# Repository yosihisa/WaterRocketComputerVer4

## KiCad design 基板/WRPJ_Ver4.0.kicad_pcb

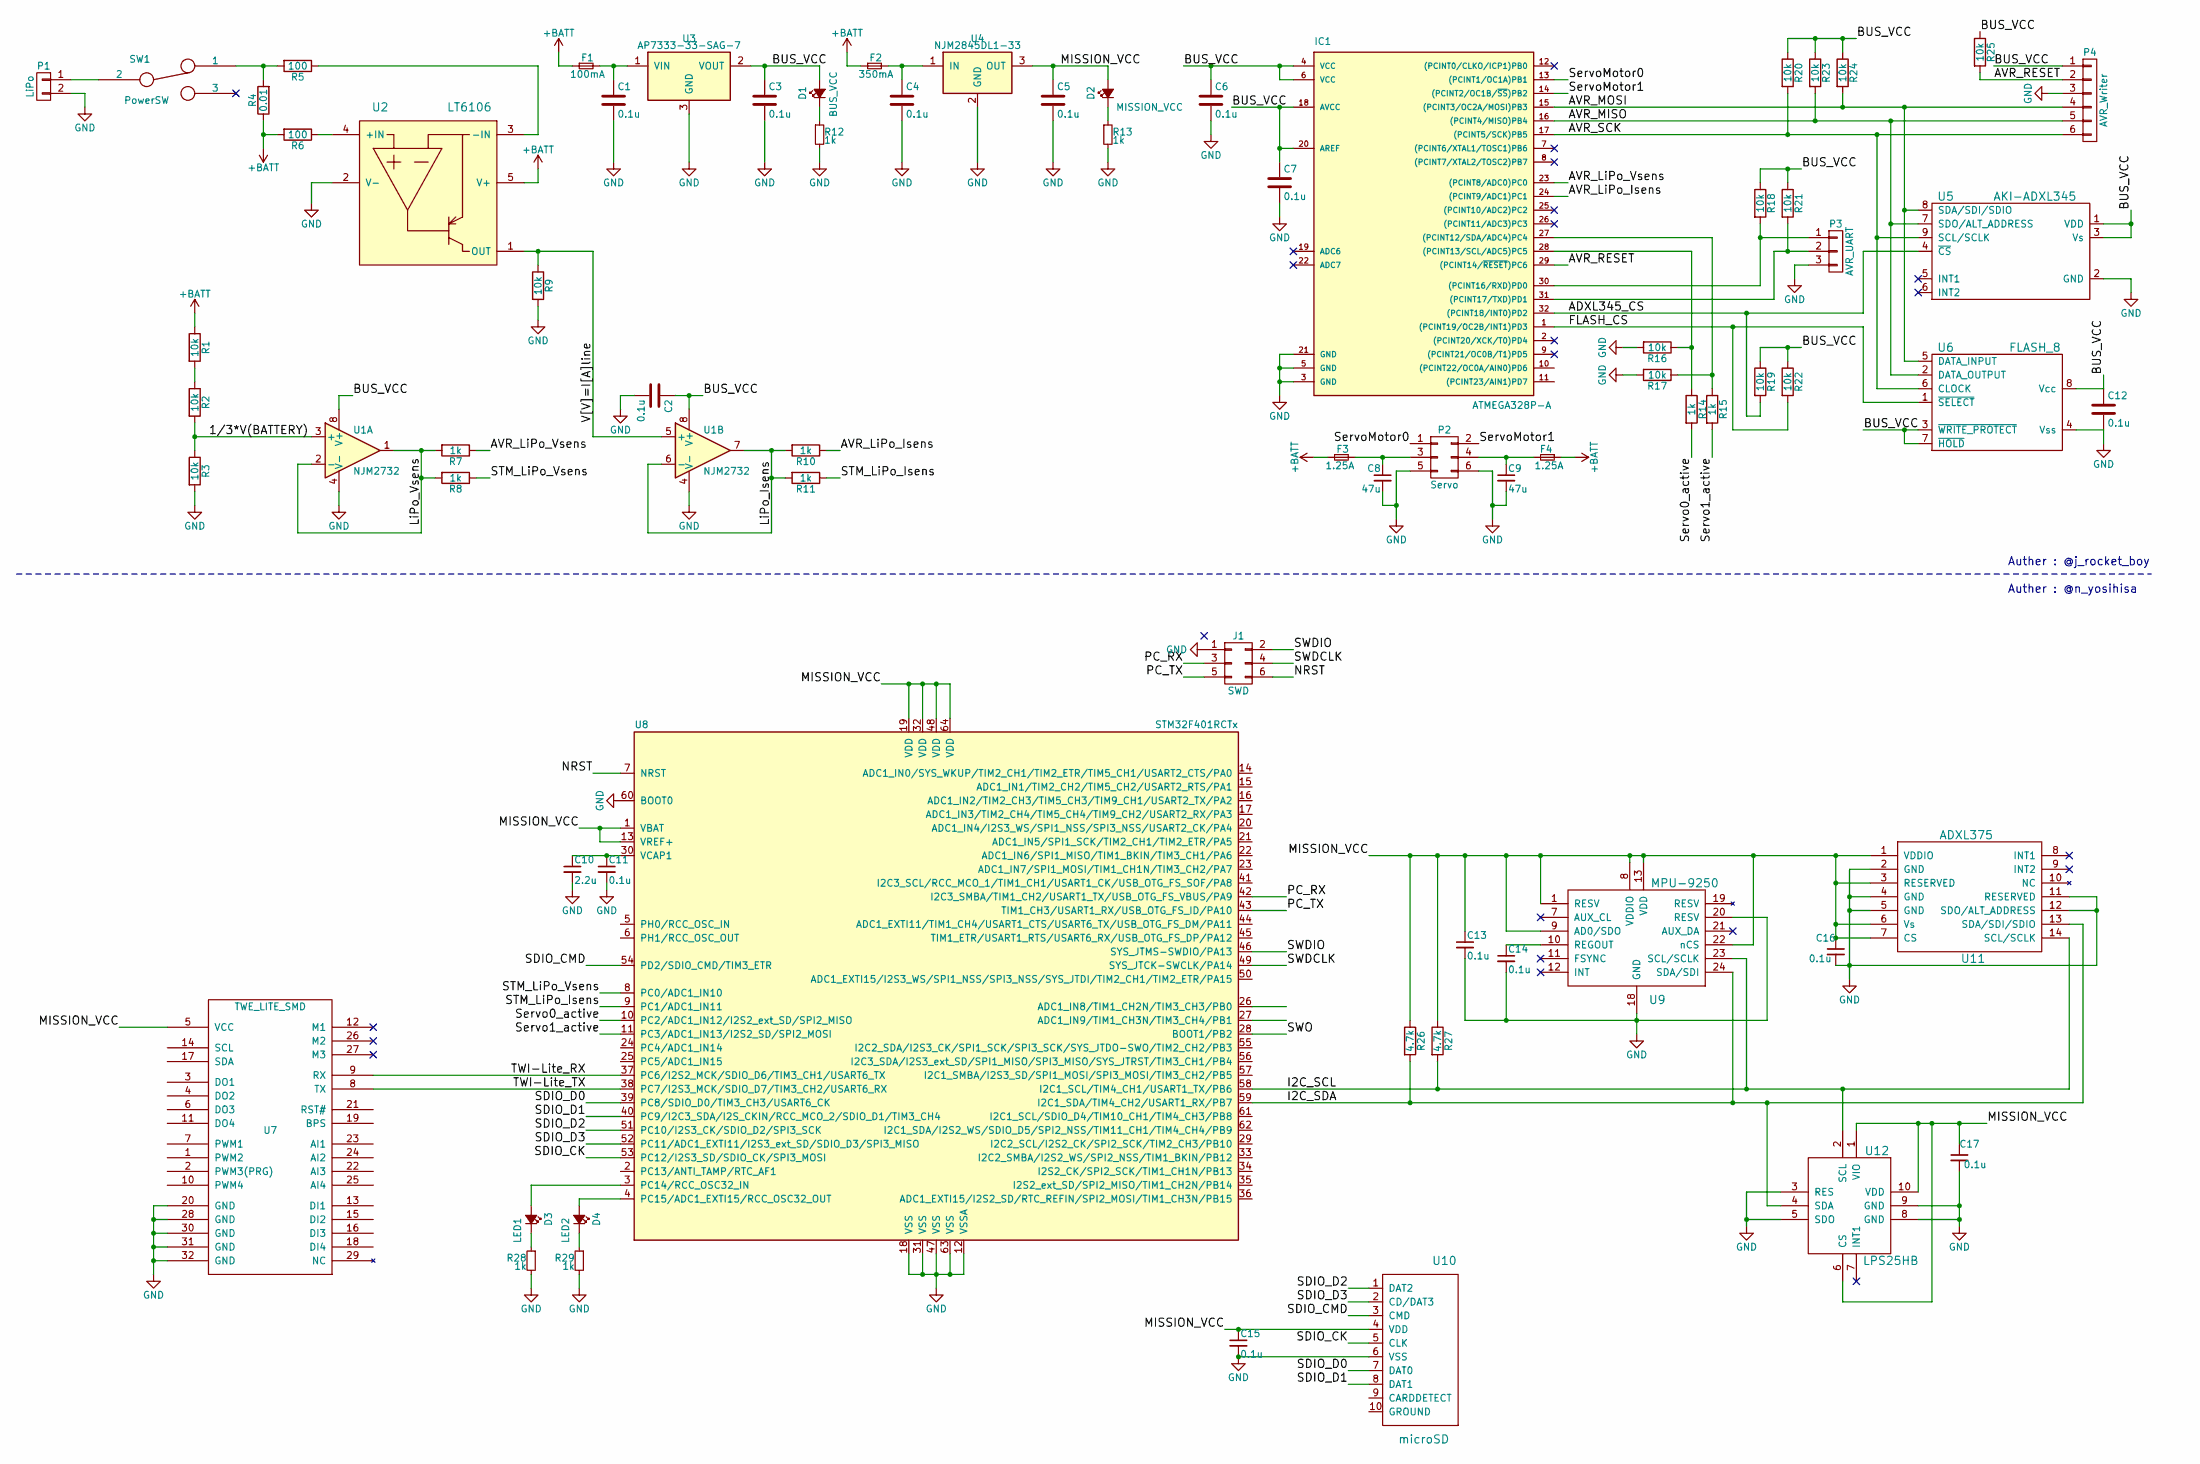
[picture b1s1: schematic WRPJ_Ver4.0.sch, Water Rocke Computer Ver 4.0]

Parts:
C1, C2, C3, C4, C5, C6, C7, C11, C12, C13, C14, C15, C16, C17: 0.1u; C_0603
C8, C9: 47u; C_1210
C10: 2.2u; C_0603
D1: BUS_VCC; LED_0603
D2: MISSION_VCC; LED_0603
D3: LED1; LED_0603
D4: LED2; LED_0603
F1: 100mA; R_1210
F2: 350mA; R_1210
F3, F4: 1.25A; R_1210
IC1: ATMEGA328P-A; LQFP-32_7x7mm_Pitch0.8mm
J1: SWD; Pin_Header_Straight_2x03_Pitch1.27mm
P1: LiPo; S2B-EH
P2: Servo; Pin_Header_Angled_2x03_Pitch2.54mm
P3: AVR_UART; Pin_Header_Straight_1x03_Pitch1.27mm
P4: AVR_Writer; Pin_Header_Straight_1x06_Pitch1.27mm
R1, R2, R3, R9, R16, R17, R18, R19, R20, R21, R22, R23, R24, R25: 10k; R_0603
R4: 0.01; R_2512
R5, R6: 100; R_0603
R7, R8, R10, R11, R12, R13, R14, R15, R28, R29: 1k; R_0603
R26, R27: 4.7k; R_0603
SW1: PowerSW; SS-12D01-VG4
U1: NJM2732; SSOP-8
U2: LT6106; SOT-23-5
U3: AP7333-33-SAG-7; SOT-23
U4: NJM2845DL1-33; TO-252-2
U5: AKI-ADXL345
U6: FLASH_8; SOIC-8-N
U7: TWE_LITE_SMD; TWE-001L-SMD
U8: STM32F401RCTx; LQFP-64_10x10mm_Pitch0.5mm
U9: MPU-9250; QFN-24_3x3mm_Pitch0.4mm
U10: microSD
U11: ADXL375; LGA_CC-14-1
U12: LPS25HB; HLGA-10L

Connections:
+BATT: F1.1, F2.1, F3.1, F4.1, R1.1, R4.1, R6.2, U2.5 (V+)
/1/3*V(BATTERY): R2.2, R3.1, U1.3 (+)
/ADXL345_CS: IC1.32 ((PCINT18/INT0)PD2), R19.2, U5.4 (~CS)
/AVR_LiPo_Isens: IC1.24 ((PCINT9/ADC1)PC1), R10.1
/AVR_LiPo_Vsens: IC1.23 ((PCINT8/ADC0)PC0), R7.1
/AVR_MISO: IC1.16 ((PCINT4/MISO)PB4), P4.5, R23.2, U5.7 (SDO/ALT_ADDRESS), U6.2 (DATA_OUTPUT)
/AVR_MOSI: IC1.15 ((PCINT3/OC2A/MOSI)PB3), P4.4, R24.2, U5.8 (SDA/SDI/SDIO), U6.5 (DATA_INPUT)
/AVR_RESET: IC1.29 ((PCINT14/~RESET~)PC6), P4.2, R25.2
/AVR_SCK: IC1.17 ((PCINT5/SCK)PB5), P4.6, R20.2, U5.9 (SCL/SCLK), U6.6 (CLOCK)
/BUS_VCC: C2.1, C3.1, C6.1, C7.1, C12.1, D1.2 (A), IC1.4 (VCC), IC1.6 (VCC), IC1.18 (AVCC), IC1.20 (AREF), P4.1, R18.1, R19.1, R20.1, R21.1, R22.1, R23.1, R24.1, R25.1, U1.8 (V+), U3.2 (VOUT), U5.1 (VDD), U5.3 (Vs), U6.3 (~WRITE_PROTECT), U6.7 (~HOLD), U6.8 (Vcc)
/FLASH_CS: IC1.1 ((PCINT19/OC2B/INT1)PD3), R22.2, U6.1 (~SELECT)
/I2C_SCL: R27.2, U8.58 (I2C1_SCL/TIM4_CH1/USART1_TX/PB6), U9.23 (SCL/SCLK), U11.14 (SCL/SCLK), U12.2 (SCL)
/I2C_SDA: R26.2, U8.59 (I2C1_SDA/TIM4_CH2/USART1_RX/PB7), U9.24 (SDA/SDI), U11.13 (SDA/SDI/SDIO), U12.4 (SDA)
/LiPo_Isens: R10.2, R11.2, U1.6 (-), U1.7
/LiPo_Vsens: R7.2, R8.2, U1.1, U1.2 (-)
/MISSION_VCC: C5.1, C13.1, C15.1, C16.1, C17.1, D2.2 (A), R26.1, R27.1, U4.3 (OUT), U7.5 (VCC), U8.1 (VBAT), U8.13 (VREF+), U8.19 (VDD), U8.32 (VDD), U8.48 (VDD), U8.64 (VDD), U9.1 (RESV), U9.8 (VDDIO), U9.9 (AD0/SDO), U9.13 (VDD), U9.22 (nCS), U10.4 (VDD), U11.1 (VDDIO), U11.3 (RESERVED), U11.6 (Vs), U11.7 (CS), U12.1 (VIO), U12.6 (CS), U12.10 (VDD)
/NRST: J1.6, U8.7 (NRST)
/PC_RX: J1.3, U8.42 (I2C3_SMBA/TIM1_CH2/USART1_TX/USB_OTG_FS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)
/PC_TX: J1.5, U8.43 (TIM1_CH3/USART1_RX/USB_OTG_FS_ID/PA10)
/SDIO_CK: U8.53 (PC12/I2S3_SD/SDIO_CK/SPI3_MOSI), U10.5 (CLK)
/SDIO_CMD: U8.54 (PD2/SDIO_CMD/TIM3_ETR), U10.3 (CMD)
/SDIO_D0: U8.39 (PC8/SDIO_D0/TIM3_CH3/USART6_CK), U10.7 (DAT0)
/SDIO_D1: U8.40 (PC9/I2C3_SDA/I2S_CKIN/RCC_MCO_2/SDIO_D1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), U10.8 (DAT1)
/SDIO_D2: U8.51 (PC10/I2S3_CK/SDIO_D2/SPI3_SCK), U10.1 (DAT2)
/SDIO_D3: U8.52 (PC11/ADC1_EXTI11/I2S3_ext_SD/SDIO_D3/SP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), U10.2 (CD/DAT3)
/STM_LiPo_Isens: R11.1, U8.9 (PC1/ADC1_IN11)
/STM_LiPo_Vsens: R8.1, U8.8 (PC0/ADC1_IN10)
/SWDCLK: J1.4, U8.49 (SYS_JTCK-SWCLK/PA14)
/SWDIO: J1.2, U8.46 (SYS_JTMS-SWDIO/PA13)
/SWO: U8.28 (BOOT1/PB2)
/Servo0_active: R14.2, U8.10 (PC2/ADC1_IN12/I2S2_ext_SD/SPI2_MISO)
/Servo1_active: R15.2, U8.11 (PC3/ADC1_IN13/I2S2_SD/SPI2_MOSI)
/ServoMotor0: IC1.13 ((PCINT1/OC1A)PB1), P2.1
/ServoMotor1: IC1.14 ((PCINT2/OC1B/~SS~)PB2), P2.2
/TWI-Lite_RX: U7.9 (RX), U8.37 (PC6/I2S2_MCK/SDIO_D6/TIM3_CH1/USART6_TX)
/TWI-Lite_TX: U7.8 (TX), U8.38 (PC7/I2S3_MCK/SDIO_D7/TIM3_CH2/USART6_RX)
/V[V]=I[A]line: R9.1, U1.5 (+), U2.1 (OUT)
GND: C1.2, C2.2, C3.2, C4.2, C5.2, C6.2, C7.2, C8.2, C9.2, C10.2, C11.2, C12.2, C13.2, C14.2, C15.2, C16.2, C17.2, IC1.3 (GND), IC1.5 (GND), IC1.21 (GND), J1.1, P1.2, P2.5, P2.6, P3.3, P4.3, R3.2, R9.2, R12.2, R13.2, R16.2, R17.2, R28.2, R29.2, U1.4 (V-), U2.2 (V-), U3.3 (GND), U4.2 (GND), U5.2 (GND), U6.4 (Vss), U7.20 (GND), U7.28 (GND), U7.30 (GND), U7.31 (GND), U7.32 (GND), U8.12 (VSSA), U8.18 (VSS), U8.31 (VSS), U8.47 (VSS), U8.60 (BOOT0), U8.63 (VSS), U9.18 (GND), U9.20 (RESV), U10.6 (VSS), U11.2 (GND), U11.4 (GND), U11.5 (GND), U11.11 (RESERVED), U11.12 (SDO/ALT_ADDRESS), U12.3 (RES), U12.5 (SDO), U12.8 (GND), U12.9 (GND)
unnamed: C1.1, F1.2, U3.1 (VIN)
unnamed: C4.1, F2.2, U4.1 (IN)
unnamed: C8.1, F3.2, P2.3
unnamed: C9.1, F4.2, P2.4
unnamed: C10.1, C11.1, U8.30 (VCAP1)
unnamed: C14.1, U9.10 (REGOUT)
unnamed: D1.1 (K), R12.1
unnamed: D2.1 (K), R13.1
unnamed: D3.1 (K), R28.1
unnamed: D3.2 (A), U8.3 (PC14/RCC_OSC32_IN)
unnamed: D4.1 (K), R29.1
unnamed: D4.2 (A), U8.4 (PC15/ADC1_EXTI15/RCC_OSC32_OUT)
unnamed: IC1.27 ((PCINT12/SDA/ADC4)PC4), R15.1, R17.1
unnamed: IC1.28 ((PCINT13/SCL/ADC5)PC5), R14.1, R16.1
unnamed: IC1.30 ((PCINT16/RXD)PD0), P3.1, R18.2
unnamed: IC1.31 ((PCINT17/TXD)PD1), P3.2, R21.2
unnamed: P1.1, SW1.2
unnamed: R1.2, R2.1
unnamed: R4.2, R5.2, SW1.1
unnamed: R5.1, U2.3 (-IN)
unnamed: R6.1, U2.4 (+IN)

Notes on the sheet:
Auther : @j_rocket_boy
Auther : @n_yosihisa

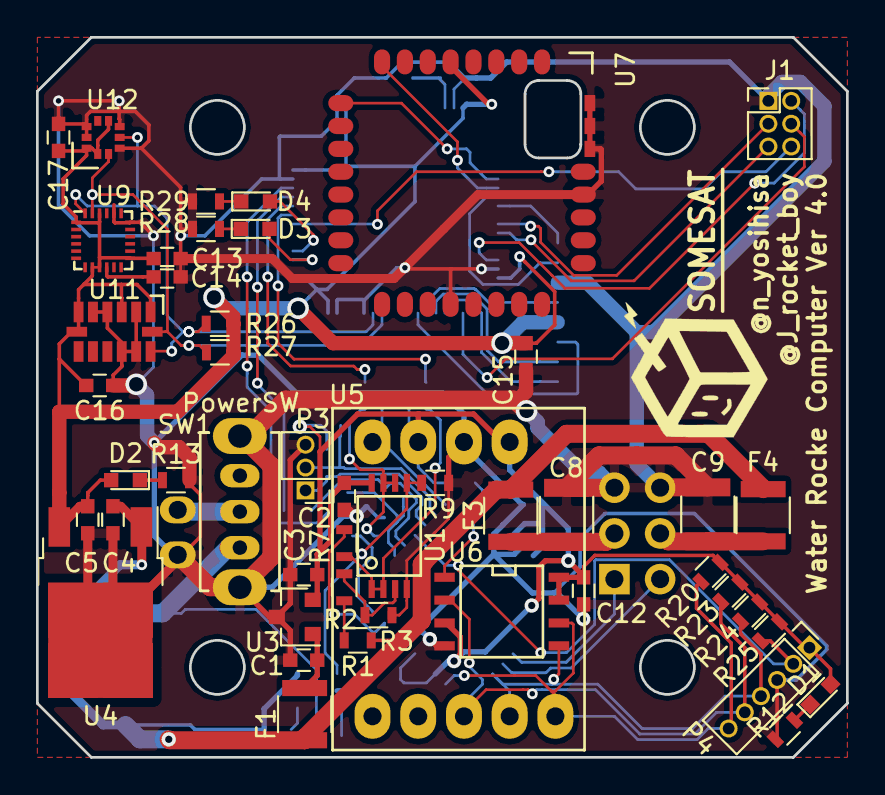
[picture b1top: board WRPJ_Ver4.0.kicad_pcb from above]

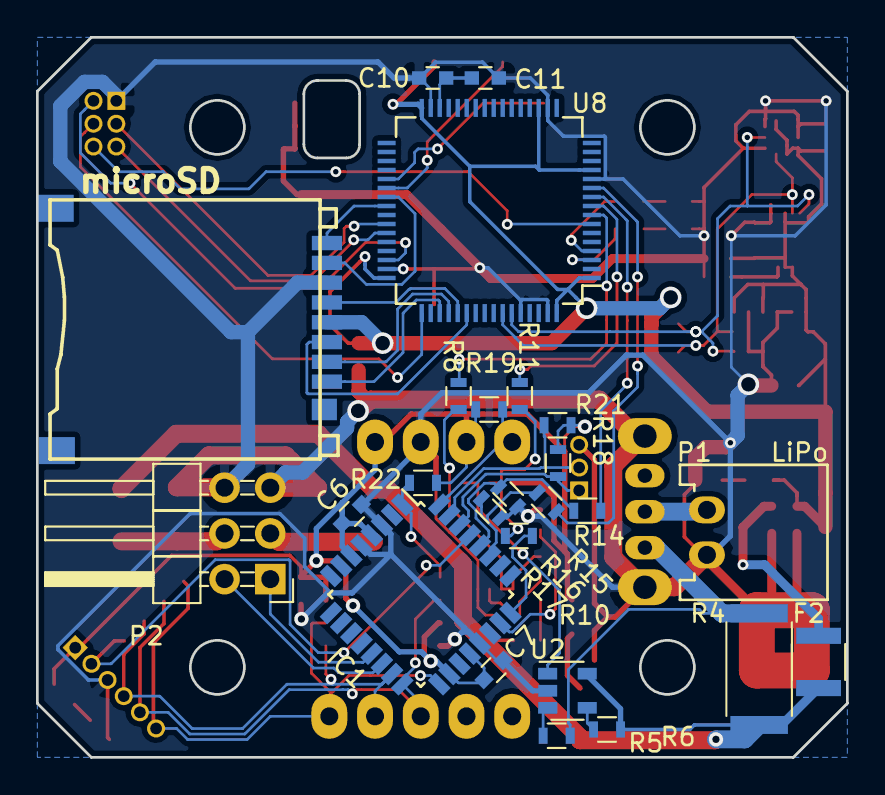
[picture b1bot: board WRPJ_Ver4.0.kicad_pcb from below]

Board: 2 copper layers, 45.0 x 40.0 mm, 73 parts (24 on the bottom side), 58 nets.

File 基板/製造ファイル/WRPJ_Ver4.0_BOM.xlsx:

Parts | Value | package | QTY | DigiKey/Mouser/Manufacturer part | Elecrow PN | Component ID | Component Part Number | Digi-Key Part Number | Remark/Link
C1,C2,C3,C4,C5,C6,C7,C11,C12,C13,C14,C15,C16,C17 | 0.1uF | 0603 | 14 | Elecrow 364 Free Compoents |  | 15331 | C14663
C10 | 2.2uF | 0603 | 1 | Elecrow 365 Free Compoents |  | 24366 | C23630
R5,R6 | 100Ω | 0603 | 2 | Elecrow 366 Free Compoents |  | 23502 | C22775
R7,R8,R10,R11,R12,R13,R14,R15,R28,R29 | 1kΩ | 0603 | 10 | Elecrow 367 Free Compoents |  | 21904 | C21190
R26,R27 | 4.7kΩ | 0603 | 2 | Elecrow 368 Free Compoents |  | 23889 | C23162
R1,R2,R3,R9,R16,R17,R18,R19,R20,R21,R22,R23,R24,R25 | 10kΩ | 0603 | 14 | Elecrow 369 Free Compoents |  | 26547 | C25804
IC1 | ATMEGA328P-AU | 32-TQFP | 1 | Elecrow | 5020532A
U6 | AT25SF041-SSHD-B | 8-SOIC | 1 | DigiKey |  |  |  | 1265-1174-5-ND | https://www.digikey.jp/product-detail/ja/adesto-technologies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
U8 | STM32F401RCTx | 64-LQFP | 1 | DigiKey |  |  |  | 497-14047-ND | https://www.digikey.jp/product-detail/ja/stmicroelectronics/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
U9 | MPU-9250 | 24-QFN | 1 | DigiKey |  |  |  | 1428-1019-1-ND | https://www.digikey.jp/product-detail/ja/tdk-invensense/MPU-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
U11 | ADXL375 | 14-VFLGA | 1 | DigiKey |  |  |  | ADXL375BCCZ-RL7CT-ND | https://www.digikey.jp/product-detail/ja/analog-devices-inc/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
U12 | LPS25HB | 10-VFLGA | 1 | DigiKey |  |  |  | 497-15070-1-ND | https://www.digikey.jp/product-detail/ja/stmicroelectronics/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

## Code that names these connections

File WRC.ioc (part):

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Mcu.Name=STM32F401R(B-C)Tx
Mcu.Package=LQFP64
Mcu.UserName=STM32F401RCTx
PA10.Mode=Asynchronous
PA10.Signal=USART1_RX
PA13.Mode=Serial_Wire
PA13.Signal=SYS_JTMS-SWDIO
PA14.Mode=Serial_Wire
PA14.Signal=SYS_JTCK-SWCLK
PA9.Mode=Asynchronous
PA9.Signal=USART1_TX
PB6.Mode=I2C
PB6.Signal=I2C1_SCL
PB7.Mode=I2C
PB7.Signal=I2C1_SDA
PC0.Signal=ADCx_IN10
PC1.Signal=ADCx_IN11
PC10.GPIOParameters=GPIO_PuPd
PC10.GPIO_PuPd=GPIO_PULLUP
PC10.Mode=SD_4_bits_Wide_bus
PC10.Signal=SDIO_D2
PC11.GPIOParameters=GPIO_PuPd
PC11.GPIO_PuPd=GPIO_PULLUP
PC11.Mode=SD_4_bits_Wide_bus
PC11.Signal=SDIO_D3
PC12.GPIOParameters=GPIO_PuPd
PC12.GPIO_PuPd=GPIO_PULLUP
PC12.Mode=SD_4_bits_Wide_bus
PC12.Signal=SDIO_CK
PC14-OSC32_IN.GPIOParameters=GPIO_Label
PC14-OSC32_IN.GPIO_Label=LED1
PC14-OSC32_IN.Signal=GPIO_Output
PC15-OSC32_OUT.GPIOParameters=GPIO_Label
PC15-OSC32_OUT.GPIO_Label=LED2
PC15-OSC32_OUT.Signal=GPIO_Output
PC2.GPIOParameters=GPIO_Label
PC2.GPIO_Label=Servo0
PC2.Signal=GPIO_Input
PC3.GPIOParameters=GPIO_Label
PC3.GPIO_Label=Servo1
PC3.Signal=GPIO_Input
PC6.Mode=Asynchronous
PC6.Signal=USART6_TX
PC7.Mode=Asynchronous
PC7.Signal=USART6_RX
PC8.GPIOParameters=GPIO_PuPd
PC8.GPIO_PuPd=GPIO_PULLUP
PC8.Mode=SD_4_bits_Wide_bus
PC8.Signal=SDIO_D0
PC9.GPIOParameters=GPIO_PuPd
PC9.GPIO_PuPd=GPIO_PULLUP
PC9.Mode=SD_4_bits_Wide_bus
PC9.Signal=SDIO_D1
PD2.GPIOParameters=GPIO_PuPd
PD2.GPIO_PuPd=GPIO_PULLUP
PD2.Mode=SD_4_bits_Wide_bus
PD2.Signal=SDIO_CMD
RCC.HSE_VALUE=25000000
RCC.SYSCLKFreq_VALUE=84000000
RCC.SYSCLKSource=RCC_SYSCLKSOURCE_PLLCLK
board=WRC

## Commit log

2017-08-11 プロジェクト ファイルを追加します。
2017-08-11 Ver1.0
